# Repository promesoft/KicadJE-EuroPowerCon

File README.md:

# KicadEuroPowerCon
Powerplane for Eurorack Doepfer connectors

## Status - Rev B board in prototest - Virtual GND fail
### Initial 
| Stage  | Detail | Status |
| ------------- | ------------- | ------------- |
| create material  | sch/pcb | produced Rev B  |
| | gerber | produced and uploaded RevB |
| production  | ordered  | OK |
|  | produced | OK |
|  | delivered | OK |
### Preliminary validation
| Test  | Detail | Status |
| ------------- | ------------- | ------------- |
| Initial Inspection | Visual - Component Mounting | OK |
| Initial Technical Test | +-20V in +9V in | OK |
| | +/-12v out +5V out | OK |
| | LED's | OK |
| Initial Product Test | Powercon burn in with 10pin VCF | OK |
| Initial Product Test | Powercon 16pin |  OK |
| Initial Product Test | Virtual GND | FAIL - see ERRATA - Working after workaround |
| Initial Product Test | 18-24V single ended bypass reg | VCO - OK |
### Secondary validation
| Test  | Detail | Status |
| ------------- | ------------- |------------- |
| Product Test | Powercon burn in 10pin | VCF ok|
| Product Test | Powercon 16pin | VCO ok|
| Quality | Linear Regulator Noise | |
| Quality | Dual 12v Switched Mode PSU Noise | |
| Quality | Single 30v Switched Mode PSU Linear Regulator Noise | |
| Quality | Single 24v Switched Mode PSU Noise | |
| | |Input noise | 
| | |GND noise |  
| | |Output Noise (no 7812/7912 reg - 0R5 resistor replaced common mode filter) | 
| Long Term Product Test | | ongoing |

### Errata
 * Q2 BD140 err in schematic - C and E flipped by mistake
 * Q2 Pin 1 and R11 connected to GND by mistake.
 
### Issues and Notes
 * fuse holder for +5V should be changed
 * virtual GND should be powered behind fuse
 * Q2 becomes warm due to higher load on the positive supply when using Virtual GND on single ended supply.
 
## Physical Construction
100x100mm
Optional cut in 2 where the top part can be used as a normal regulator board.

## Features
+/- 12V Supply
 - Requires +-14,5v to +-27v. Input can be either linear transformer with/without bridge rectifier, or switched mode. 
 - Max 1,5A will require additional cooling of the regulators and larger diodes.
 - Optional disable regulation
 - Optional synthetic GND if only single ended supply is available.
 
+5V Supply
 - Requires 7-25V input either as linear transformer with/without bridge rectifier, or switched mode PSU.
 - Optional input from +15V thru supply 
 - Max 1,5A will require additional cooling of the regulators and larger diodes.
 - Optional disable regulation

Thru
 - Both 7V and +-15 input sections can be sent thru to a second module for daisy chaining of modules.

Reg out
 - Regulated outputs can be send out to other power distribution modules or directly to Synth modules that does not require the Doepfer 10pin or 16pin power input.
 
## Board Layout
- Top - Power in
- Top Right - Regulated power out
- Bottom - Doepfer Powercon

# Electrical Construction
Intended function

## Schematic

## 3D

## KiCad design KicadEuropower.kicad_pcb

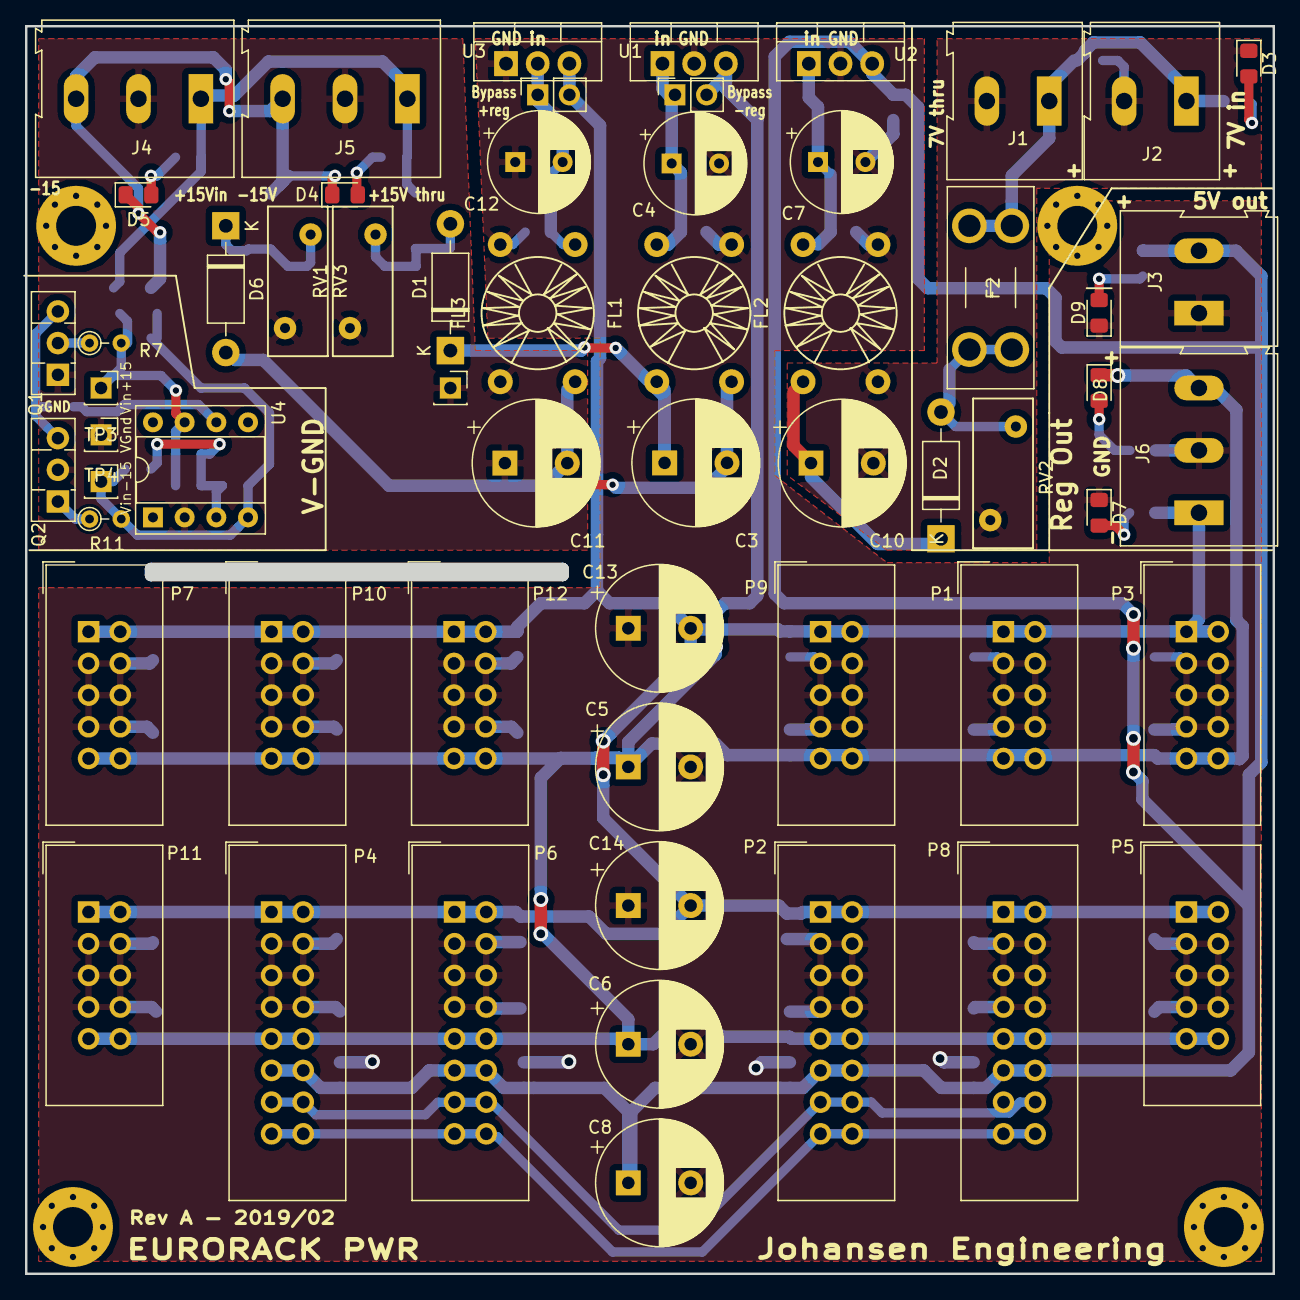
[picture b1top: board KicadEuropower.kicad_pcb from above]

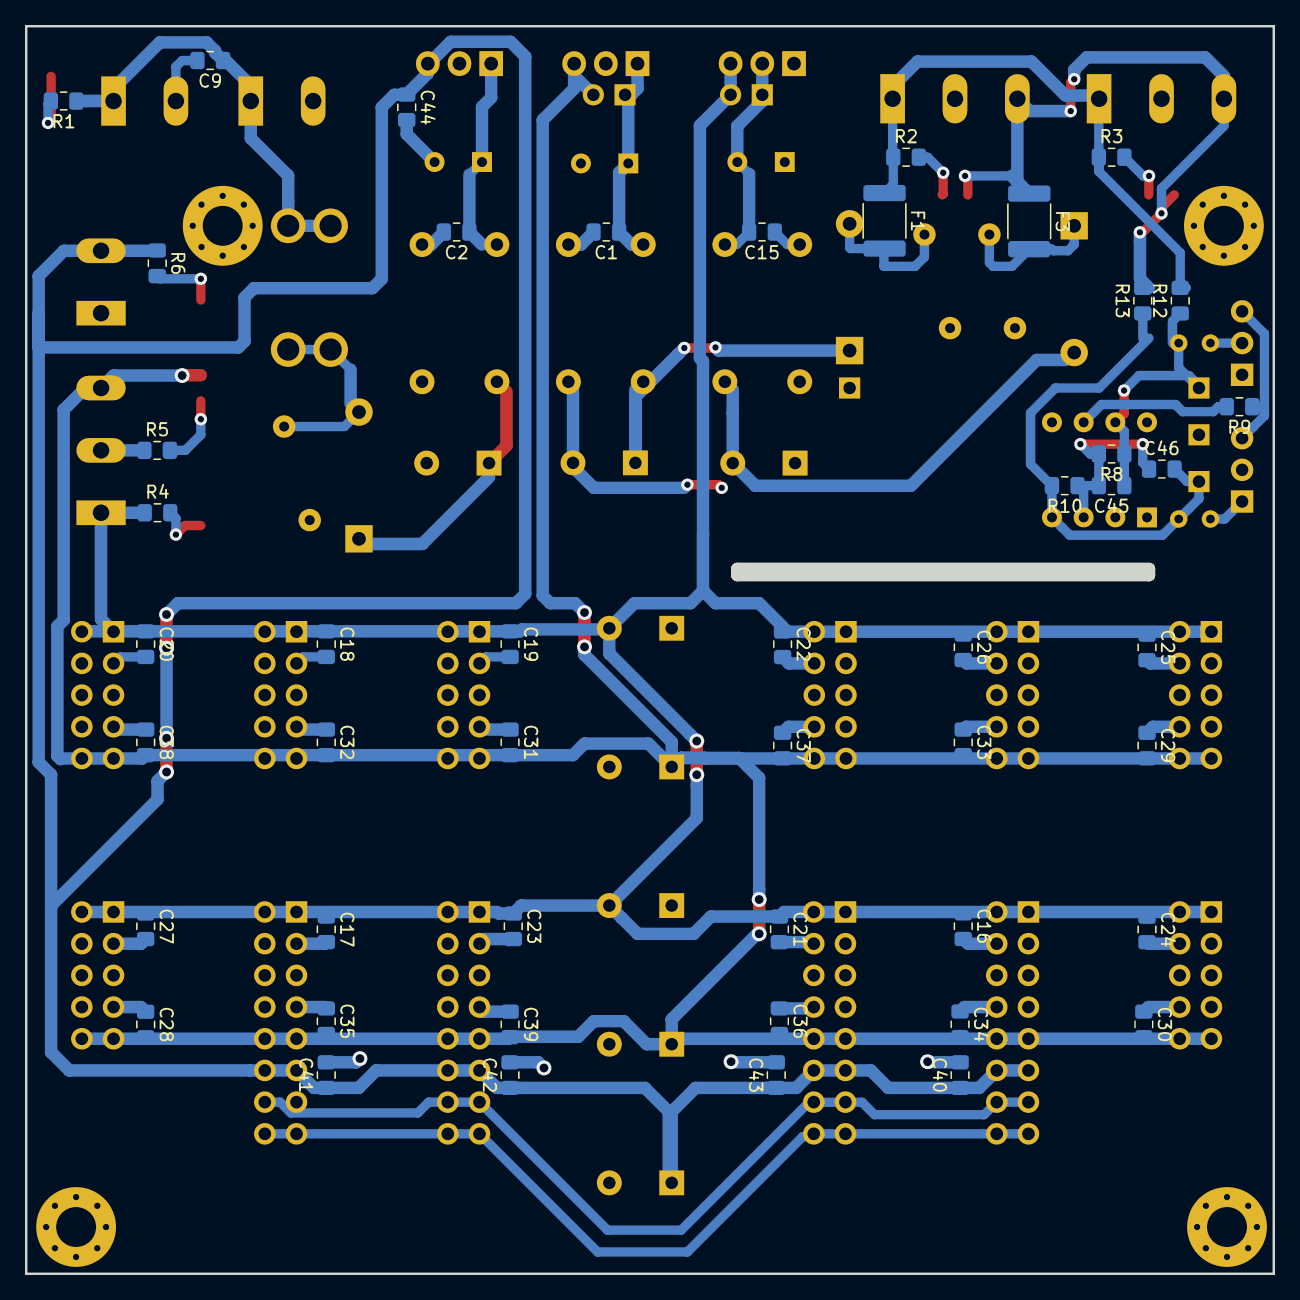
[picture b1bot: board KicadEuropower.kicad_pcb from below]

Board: 2 copper layers, 100.0 x 100.0 mm, 107 parts (48 on the bottom side), 33 nets.

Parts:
C1, C2, C9, C15, C16, C17, C18, C19, C20, C21, C22, C23, C24, C25, C26, C27, C28, C29, C30, C31, C32, C33, C34, C35, C36, C37, C38, C39, C40, C41, C42, C43, C44: 100n; C_0805_2012Metric_Pad1.15x1.40mm_HandSolder
C3, C5, C6, C8, C10, C11, C13, C14: 1000uF; CP_Radial_D10.0mm_P5.00mm
C4, C7, C12: 1000uF; CP_Radial_D8.0mm_P3.80mm
C45, C46: 220n; C_0805_2012Metric_Pad1.15x1.40mm_HandSolder
D1, D2, D6: 1N4001; D_DO-41_SOD81_P10.16mm_Horizontal
D3, D4, D5, D7, D8, D9: LED; LED_0805_2012Metric_Pad1.15x1.40mm_HandSolder
F1, F3: Fuse_Small; Fuse_1812_4532Metric_Pad1.30x3.40mm_HandSolder
F2: Fuse_Small; Fuseholder_Blade_Mini_Keystone_3568
FL1, FL2, FL3: EMI_Filter_CommonMode; Transformer_Toroid_horizontal_Diameter9mm_Amidon-T30
J1, J2, J3: Conn_01x02_Male; TerminalBlock_Altech_AK300-2_P5.00mm
J4, J5, J6: Conn_01x03_Male; TerminalBlock_Altech_AK300-3_P5.00mm
JP1, JP2: Jumper_2_Open; PinSocket_1x02_P2.54mm_Vertical
P1, P3, P5, P7, P9, P10, P11, P12: Doepfer_Power_10pin; IDC-Header_2x05_Pitch2.54mm_Straight
P2, P4, P6, P8: Doepfer_Power_16pin; IDC-Header_2x08_Pitch2.54mm_Straight
Q1: BD139; TO-126-3_Vertical
Q2: BD140; TO-126-3_Vertical
R1, R6: 680R; R_0805_2012Metric_Pad1.15x1.40mm_HandSolder
R2, R3: 3k3; R_0805_2012Metric_Pad1.15x1.40mm_HandSolder
R4, R5: 1k5; R_0805_2012Metric_Pad1.15x1.40mm_HandSolder
R7, R11: 10r; R_Axial_DIN0204_L3.6mm_D1.6mm_P2.54mm_Vertical
R8, R9, R10: 330r; R_0805_2012Metric_Pad1.15x1.40mm_HandSolder
R12, R13: 0R; R_0805_2012Metric_Pad1.15x1.40mm_HandSolder
RV1, RV2, RV3: Varistor; RV_Disc_D12mm_W4.8mm_P7.5mm
TP1, TP3: VGnd; PinSocket_1x01_P2.54mm_Vertical
TP2: Vin+15; PinSocket_1x01_P2.54mm_Vertical
TP4: Vin-15; PinSocket_1x01_P2.54mm_Vertical
U1: LM7812_TO220; TO-220-3_Vertical
U2: LM7805_TO220; TO-220-3_Vertical
U3: LM7912_TO220; TO-220-3_Vertical
U4: TL071; DIP-8_W7.62mm_Socket

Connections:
+5V: C8.1, C40.1, C41.1, C42.1, C43.1, C44.1, J3.2, P2.11, P2.12, P4.11, P4.12, P6.11, P6.12, P8.11, P8.12, R6.1, U2.3
+12V: C5.1, C6.1, C28.2, C29.2, C30.2, C31.2, C32.2, C33.2, C34.2, C35.2, C36.2, C37.2, C38.2, C39.2, D8.1, J6.3, JP1.2, P1.9, P1.10, P2.9, P2.10, P3.9, P3.10, P4.9, P4.10, P5.9, P5.10, P6.9, P6.10, P7.9, P7.10, P8.9, P8.10, P9.9, P9.10, P10.9, P10.10, P11.9, P11.10, P12.9, P12.10, U1.3
-12V: C13.2, C14.2, C16.1, C17.1, C18.1, C19.1, C20.1, C21.1, C22.1, C23.1, C24.1, C25.1, C26.1, C27.1, J6.1, JP2.2, P1.1, P1.2, P2.1, P2.2, P3.1, P3.2, P4.1, P4.2, P5.1, P5.2, P6.1, P6.2, P7.1, P7.2, P8.1, P8.2, P9.1, P9.2, P10.1, P10.2, P11.1, P11.2, P12.1, P12.2, R4.1, U3.3
/+5V-ext: C9.1, F2.1, J1.1, J2.1, R1.1
/+15v-int: C1.1, C4.1, FL1.4, JP1.1, U1.1
/-15v-int: C12.2, C15.2, FL3.2, JP2.1, U3.2
CV: P2.13, P2.14, P4.13, P4.14, P6.13, P6.14, P8.13, P8.14
GND: C1.2, C2.2, C4.2, C5.2, C6.2, C7.2, C8.2, C12.1, C13.1, C14.1, C15.1, C16.2, C17.2, C18.2, C19.2, C20.2, C21.2, C22.2, C23.2, C24.2, C25.2, C26.2, C27.2, C28.1, C29.1, C30.1, C31.1, C32.1, C33.1, C34.1, C35.1, C36.1, C37.1, C38.1, C39.1, C40.2, C41.2, C42.2, C43.2, C44.2, D7.1, D9.1, FL1.2, FL2.2, FL3.4, J3.1, J6.2, P1.3, P1.4, P1.5, P1.6, P1.7, P1.8, P2.3, P2.4, P2.5, P2.6, P2.7, P2.8, P3.3, P3.4, P3.5, P3.6, P3.7, P3.8, P4.3, P4.4, P4.5, P4.6, P4.7, P4.8, P5.3, P5.4, P5.5, P5.6, P5.7, P5.8, P6.3, P6.4, P6.5, P6.6, P6.7, P6.8, P7.3, P7.4, P7.5, P7.6, P7.7, P7.8, P8.3, P8.4, P8.5, P8.6, P8.7, P8.8, P9.3, P9.4, P9.5, P9.6, P9.7, P9.8, P10.3, P10.4, P10.5, P10.6, P10.7, P10.8, P11.3, P11.4, P11.5, P11.6, P11.7, P11.8, P12.3, P12.4, P12.5, P12.6, P12.7, P12.8, R5.1, U1.2, U2.2, U3.1
GNDPWR: C9.2, C10.2, D3.1, FL2.1, J1.2, J2.2, RV2.2
Gate: P2.15, P2.16, P4.15, P4.16, P6.15, P6.16, P8.15, P8.16
unnamed: C2.1, C7.1, FL2.4, U2.1
unnamed: C3.1, D1.1, FL1.3
unnamed: C10.1, D2.1, FL2.3
unnamed: C11.2, D6.2, FL3.1
unnamed: C45.1, R7.2, R8.1, R12.1, TP2.1, U4.7
unnamed: C45.2, C46.1, R8.2, R10.1, U4.3
unnamed: C46.2, R10.2, R11.2, R13.1, TP4.1, U4.4
unnamed: D1.2, F1.2, RV1.1
unnamed: D2.2, F2.2, RV2.1
unnamed: D3.2, R1.2
unnamed: D4.2, R2.2
unnamed: D5.2, R3.2
unnamed: D6.1, F3.2, RV3.2
unnamed: D7.2, R4.2
unnamed: D8.2, R5.2
unnamed: D9.2, R6.2
unnamed: Q1.2, R7.1
unnamed: Q1.3, Q2.3, R9.1
unnamed: Q2.1, R11.1
unnamed: R9.2, U4.6
Vin+15: F1.1, J4.1, J5.1, R2.1, R3.1, R12.2
Vin-15: D4.1, D5.1, F3.1, J4.3, J5.3, R13.2
VinGND: C3.2, C11.1, FL1.1, FL3.3, J4.2, J5.2, Q1.1, Q2.2, RV1.2, RV3.1, TP1.1, TP3.1, U4.2

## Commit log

2019-01-07 Getting started
2019-01-07 +5V +/-12 sch
2019-01-07 PCB Placement started
2019-01-08 3D shapes init
2019-01-08 Footprint updates
2019-01-08 Power upd and 2x10pin removed
2019-01-08 Component placement update
2019-01-08 Virtual GND
2019-01-08 Mounting holes and Text
2019-01-08 Groundplanes placed
2019-01-08 Rev A - Mechanical + Component placement + Text
2019-01-08 Fixed missing +12V on several connectors
2019-01-08 DRC ok
2019-01-08 Added SMD 0R to Virtual GND pwr feed
2019-01-08 Cleared zones around mounting holes - 3D rendered img
2019-01-08 Gerber
2019-01-09 Minor Update to PCB - New Gerber
2019-01-12 Optional TO252 regulators and added mounting holes
2019-01-14 Extra reg
2019-01-14 RevB Images
2019-01-15 Rev B Gerber
    Gerber export
    Schematic Update (visual)
    Cleanup of Rev A
2019-02-21 Rev C prepare
2019-02-21 Diode bridge replacing diodes in +-12v - VGND gets fused pwr - +5V on 1812 fuse
2019-02-21 fuses +5V and +-12 changed to 1210
2019-03-03 SCH fixed VGND err
2019-03-04 Measurements
2019-03-04 rename pict
2019-03-04 remove space in png naming so they will display in the ReadMe.md
2019-03-05 75khz FFT of noise floor
